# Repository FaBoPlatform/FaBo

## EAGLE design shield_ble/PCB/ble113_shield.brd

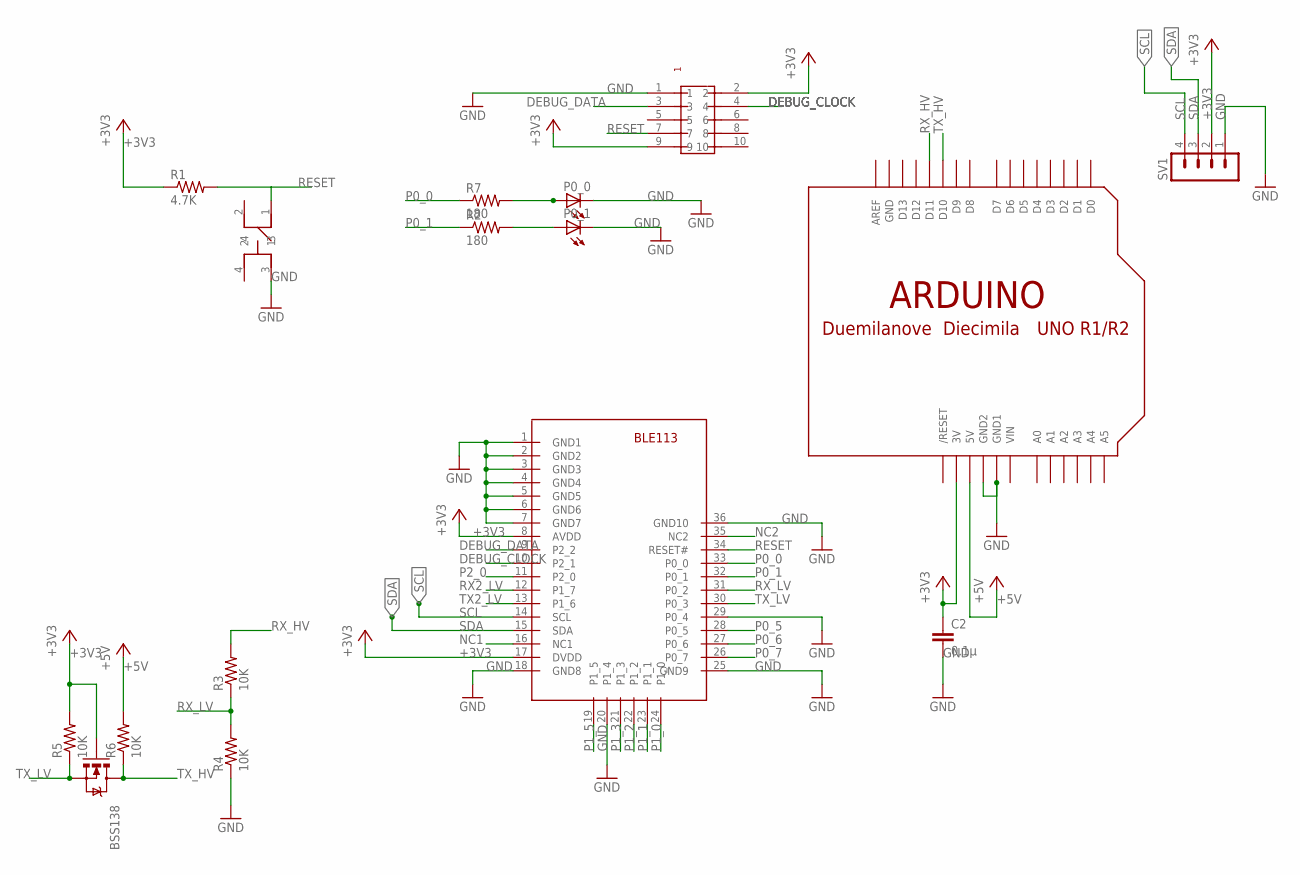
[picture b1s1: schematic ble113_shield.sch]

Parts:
BSS138: MOSFET-NCHANNELSMD; SOT23-3
C2: 0.1μ; 0603-CAP
P0_0, P0_1: LED_ESML0603; LED_SML0603
R1: 4.7K; 0603-RES
R2, R7: 180; 0603-RES
R3, R4, R5, R6: 10K; 0603-RES
SV1: MA04-1
U$1: PIN-HEADER-SMT(1.27MM)2X5
U$4: SWITCH-LS6J2M-T; SWICTH-LS6J2M-T
U$6: BLUEGIGA-BLE113
U$7: ARDUINOUNO; ARDUINO

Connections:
+3V3: BSS138.1 (G), C2.1, R1.1, R5.2, SV1.2, U$1.2, U$1.9, U$6.8 (AVDD), U$6.17 (DVDD), U$7.3V
+5V: R6.2, U$7.5V
DEBUG_CLOCK: U$1.4, U$6.10 (P2_1)
DEBUG_DATA: U$1.3, U$6.9 (P2_2)
GND: C2.2, P0_0.C, P0_1.C, R4.1, SV1.1, U$1.1, U$4.3, U$6.1 (GND1), U$6.2 (GND2), U$6.3 (GND3), U$6.4 (GND4), U$6.5 (GND5), U$6.6 (GND6), U$6.7 (GND7), U$6.18 (GND8), U$6.20 (P1_4), U$6.25 (GND9), U$6.29 (P0_4), U$6.36 (GND10), U$7.GND, U$7.GND1, U$7.GND2
unnamed: P0_0.A, R7.2
unnamed: P0_1.A, R2.2
NC1: U$6.16 (NC1)
NC2: U$6.35 (NC2)
P0_0: R7.1, U$6.33 (P0_0)
P0_1: R2.1, U$6.32 (P0_1)
P0_5: U$6.28 (P0_5)
P0_6: U$6.27 (P0_6)
P0_7: U$6.26 (P0_7)
P1_0: U$6.24 (P1_0)
P1_1: U$6.23 (P1_1)
P1_2: U$6.22 (P1_2)
P1_3: U$6.21 (P1_3)
P1_5: U$6.19 (P1_5)
P2_0: U$6.11 (P2_0)
RESET: R1.2, U$1.7, U$4.1, U$6.34 (RESET#)
RX2_LV: U$6.12 (P1_7)
RX_HV: R3.2, U$7.D11
RX_LV: R3.1, R4.2, U$6.31 (P0_2)
SCL: SV1.4, U$6.14 (SCL)
SDA: SV1.3, U$6.15 (SDA)
TX2_LV: U$6.13 (P1_6)
TX_HV: BSS138.3 (D), R6.1, U$7.D10
TX_LV: BSS138.2 (S), R5.1, U$6.30 (P0_3)
VIN: U$7.VIN

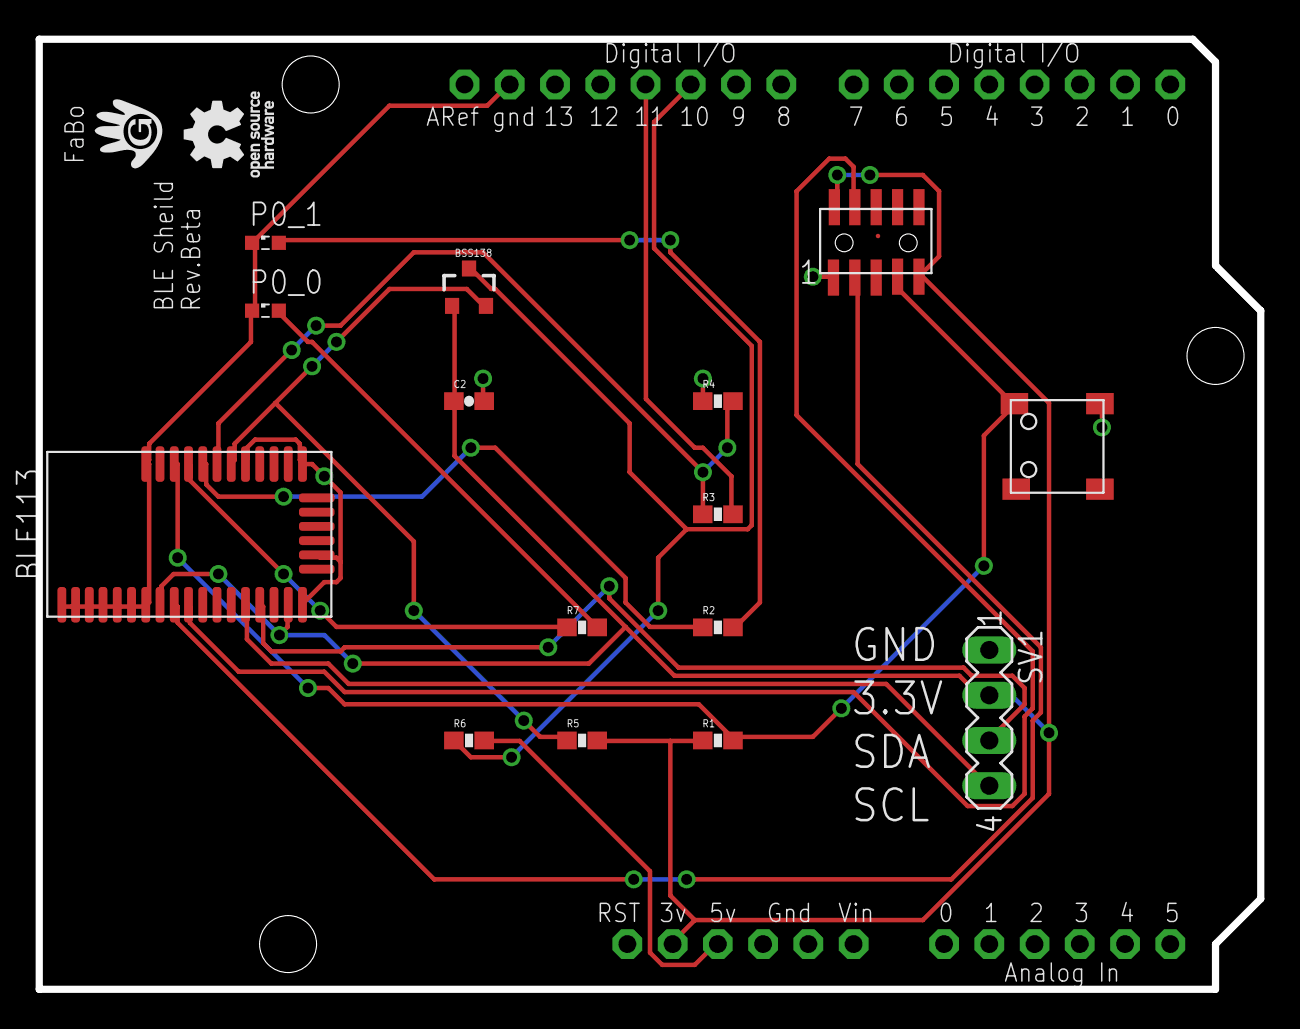
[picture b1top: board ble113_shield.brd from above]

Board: 2 copper layers, 68.6 x 53.3 mm, 18 parts (0 on the bottom side), 16 nets.

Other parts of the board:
U$2: LOGO_FABO_M
U$3: LOGO_OSHW_T_M

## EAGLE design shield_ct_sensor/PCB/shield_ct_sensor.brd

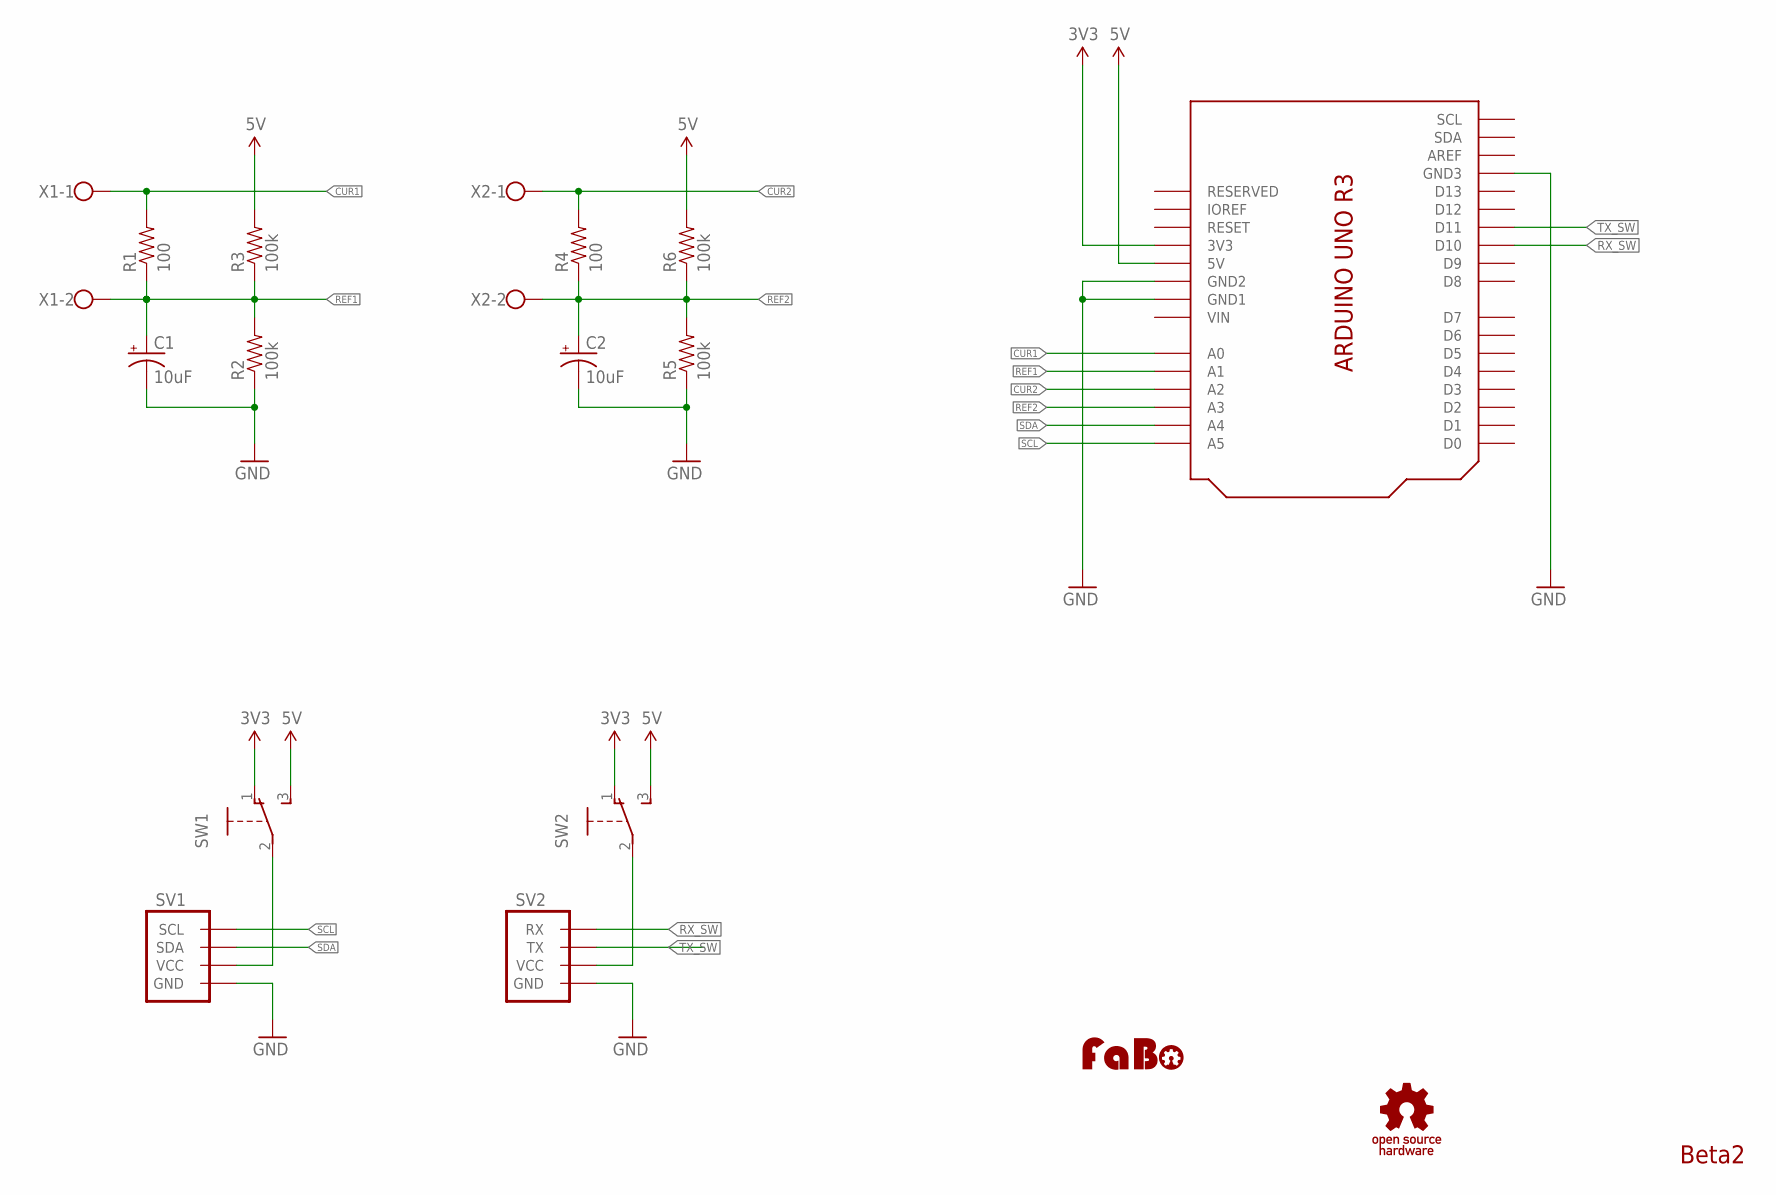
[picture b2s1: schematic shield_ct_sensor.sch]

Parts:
C1, C2: 10uF; CAP-POL-AXL-5MM
R1, R4: 100; RES-AXL-REGULAR
R2, R3, R5, R6: 100k; RES-AXL-REGULAR
SV1: BRICK_I2C_CONNECTOR
SV2: BRICK_SERIAL_CONNECTOR
SW1, SW2: SWITCH-SLIDE-EG1218; EG1218
U1: ARDUINO_UNO_R3_SHIELD; ARDUINO_UNO_R3
U$2: LOGO_FABO-M; LOGO_FABO_M
U$3: LOGO_OSHW_T-M; LOGO_OSHW_T_M
X1, X2: W237-102

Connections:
3V3: SW1.1, SW2.1, U1.3V3
5V: R3.P$2 (2), R6.P$2 (2), SW1.3, SW2.3, U1.5V
CUR1: R1.P$2 (2), U1.A0, X1.1
CUR2: R4.P$2 (2), U1.A2, X2.1
GND: C1.-, C2.-, R2.P$1 (1), R5.P$1 (1), SV1.GND, SV2.GND, U1.GND1, U1.GND2, U1.GND3
unnamed: SV2.VCC, SW2.2
unnamed: SV1.VCC, SW1.2
REF1: C1.+, R1.P$1 (1), R2.P$2 (2), R3.P$1 (1), U1.A1, X1.2
REF2: C2.+, R4.P$1 (1), R5.P$2 (2), R6.P$1 (1), U1.A3, X2.2
RX_SW: SV2.RX, U1.D10
SCL: SV1.SCL, U1.A5
SDA: SV1.SDA, U1.A4
TX_SW: SV2.TX, U1.D11
VIN: U1.VIN

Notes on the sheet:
Beta2

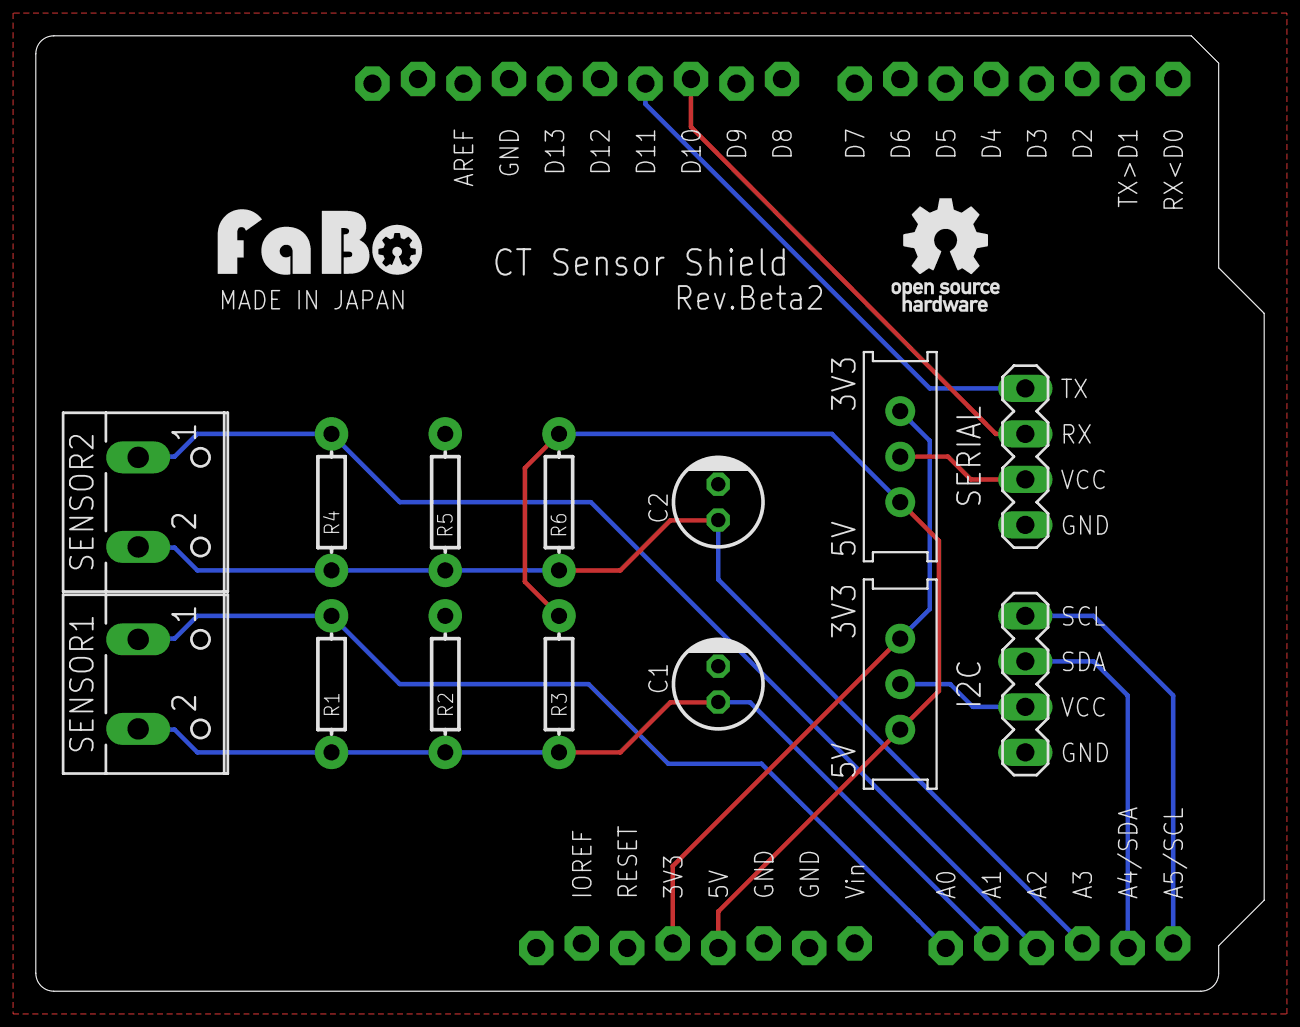
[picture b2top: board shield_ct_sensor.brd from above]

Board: 2 copper layers, 68.6 x 53.3 mm, 17 parts (0 on the bottom side), 13 nets.

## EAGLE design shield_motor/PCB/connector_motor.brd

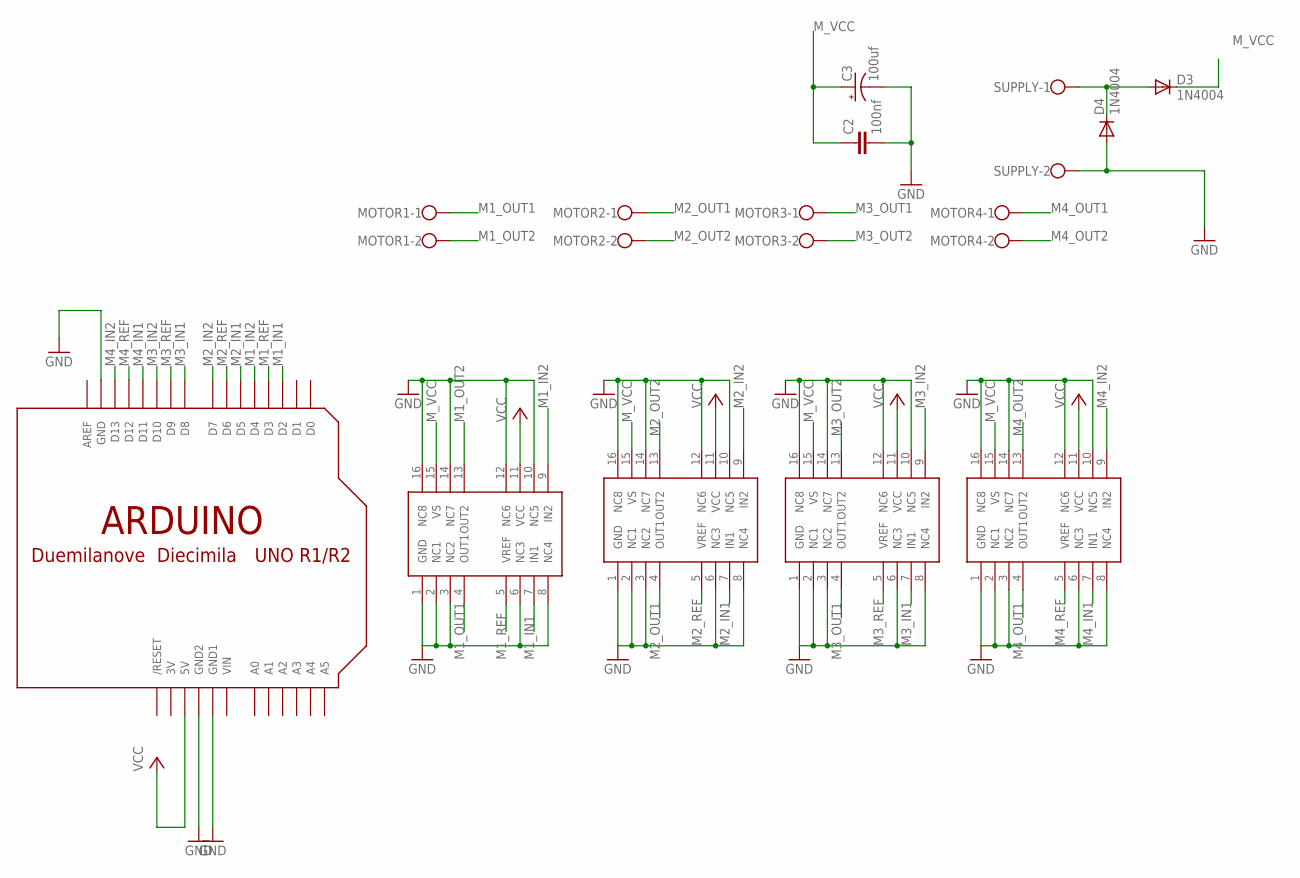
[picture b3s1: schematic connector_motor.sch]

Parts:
C2: 100nf; C0603
C3: 100uf; 153CLV-0405
D3, D4: 1N4004; DO41-10
MOTOR1, MOTOR2, MOTOR3, MOTOR4: W237-102
SUPPLY: W237-102
U$1: ARDUINO-NOHOLE
U$2, U$3, U$4, U$5: MOTOR-DRIVER-TA7281FG; MOTOR-DRIVER-TA7291FG

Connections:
3V: U$1.3V
GND: C2.2, C3.-, D4.A, SUPPLY.2, U$1.GND, U$1.GND1, U$1.GND2, U$2.1 (GND), U$2.2 (NC1), U$2.3 (NC2), U$2.6 (NC3), U$2.8 (NC4), U$2.10 (NC5), U$2.12 (NC6), U$2.14 (NC7), U$2.16 (NC8), U$3.1 (GND), U$3.2 (NC1), U$3.3 (NC2), U$3.6 (NC3), U$3.8 (NC4), U$3.10 (NC5), U$3.12 (NC6), U$3.14 (NC7), U$3.16 (NC8), U$4.1 (GND), U$4.2 (NC1), U$4.3 (NC2), U$4.6 (NC3), U$4.8 (NC4), U$4.10 (NC5), U$4.12 (NC6), U$4.14 (NC7), U$4.16 (NC8), U$5.1 (GND), U$5.2 (NC1), U$5.3 (NC2), U$5.6 (NC3), U$5.8 (NC4), U$5.10 (NC5), U$5.12 (NC6), U$5.14 (NC7), U$5.16 (NC8)
M1_IN1: U$1.D2, U$3.7 (IN1)
M1_IN2: U$1.D4, U$3.9 (IN2)
M1_OUT1: MOTOR1.1, U$3.4 (OUT1)
M1_OUT2: MOTOR1.2, U$3.13 (OUT2)
M1_REF: U$1.D3, U$3.5 (VREF)
M2_IN1: U$1.D5, U$4.7 (IN1)
M2_IN2: U$1.D7, U$4.9 (IN2)
M2_OUT1: MOTOR2.1, U$4.4 (OUT1)
M2_OUT2: MOTOR2.2, U$4.13 (OUT2)
M2_REF: U$1.D6, U$4.5 (VREF)
M3_IN1: U$1.D8, U$2.7 (IN1)
M3_IN2: U$1.D10, U$2.9 (IN2)
M3_OUT1: MOTOR3.1, U$2.4 (OUT1)
M3_OUT2: MOTOR3.2, U$2.13 (OUT2)
M3_REF: U$1.D9, U$2.5 (VREF)
M4_IN1: U$1.D11, U$5.7 (IN1)
M4_IN2: U$1.D13, U$5.9 (IN2)
M4_OUT1: MOTOR4.1, U$5.4 (OUT1)
M4_OUT2: MOTOR4.2, U$5.13 (OUT2)
M4_REF: U$1.D12, U$5.5 (VREF)
M_VCC: C2.1, C3.+, D3.C, U$2.15 (VS), U$3.15 (VS), U$4.15 (VS), U$5.15 (VS)
unnamed: D3.A, D4.C, SUPPLY.1
VCC: U$1.5V, U$2.11 (VCC), U$3.11 (VCC), U$4.11 (VCC), U$5.11 (VCC)
VIN: U$1.VIN

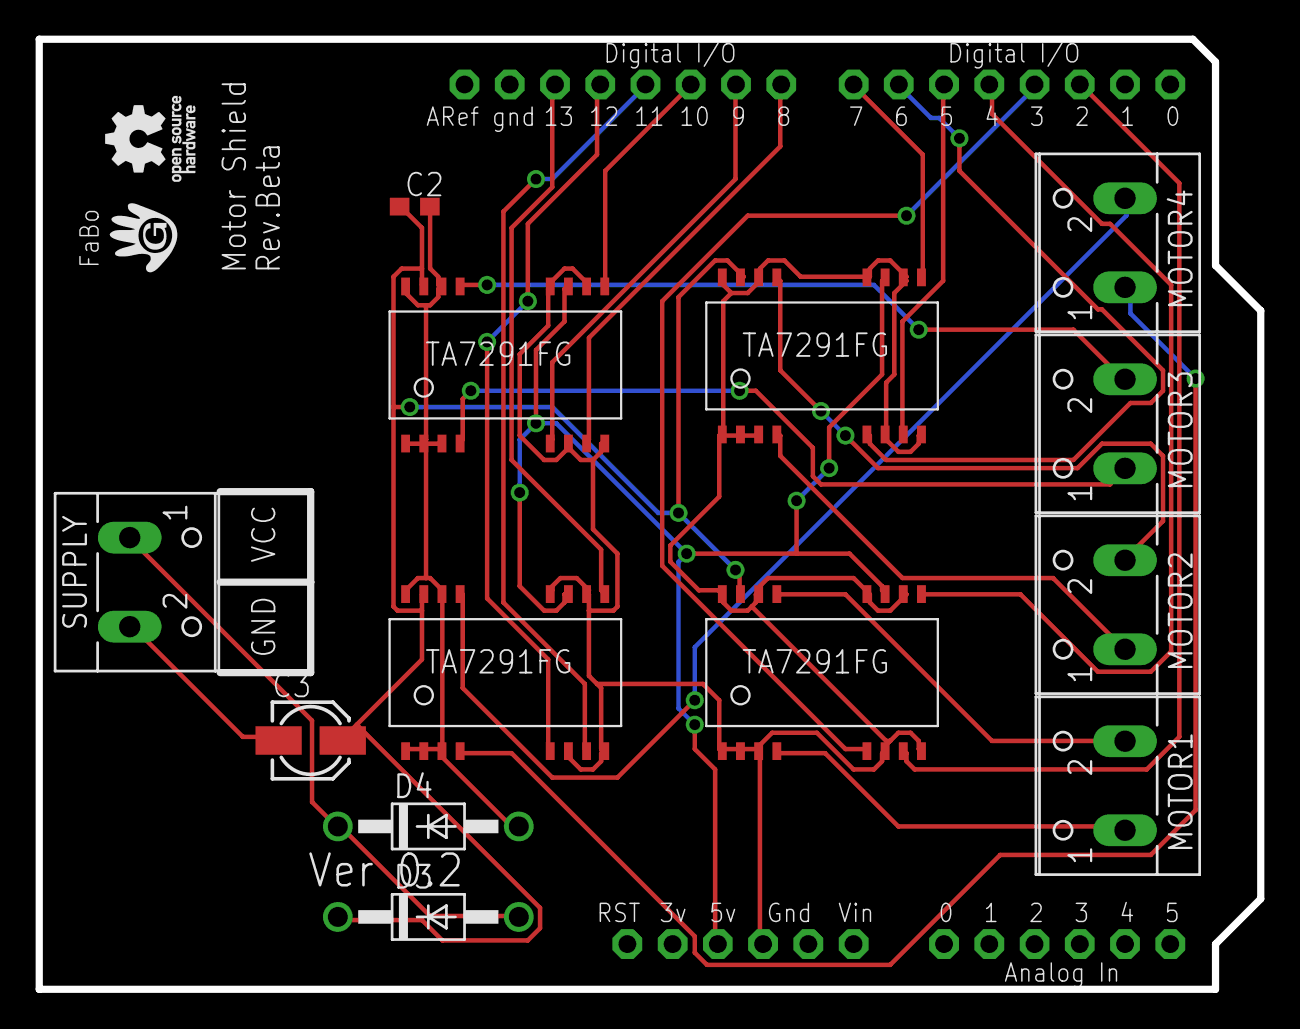
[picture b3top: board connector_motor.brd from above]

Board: 2 copper layers, 68.6 x 53.3 mm, 16 parts (0 on the bottom side), 24 nets.

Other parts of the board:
U$6: LOGO_OSHW_T_M
U$7: LOGO_FABO_M

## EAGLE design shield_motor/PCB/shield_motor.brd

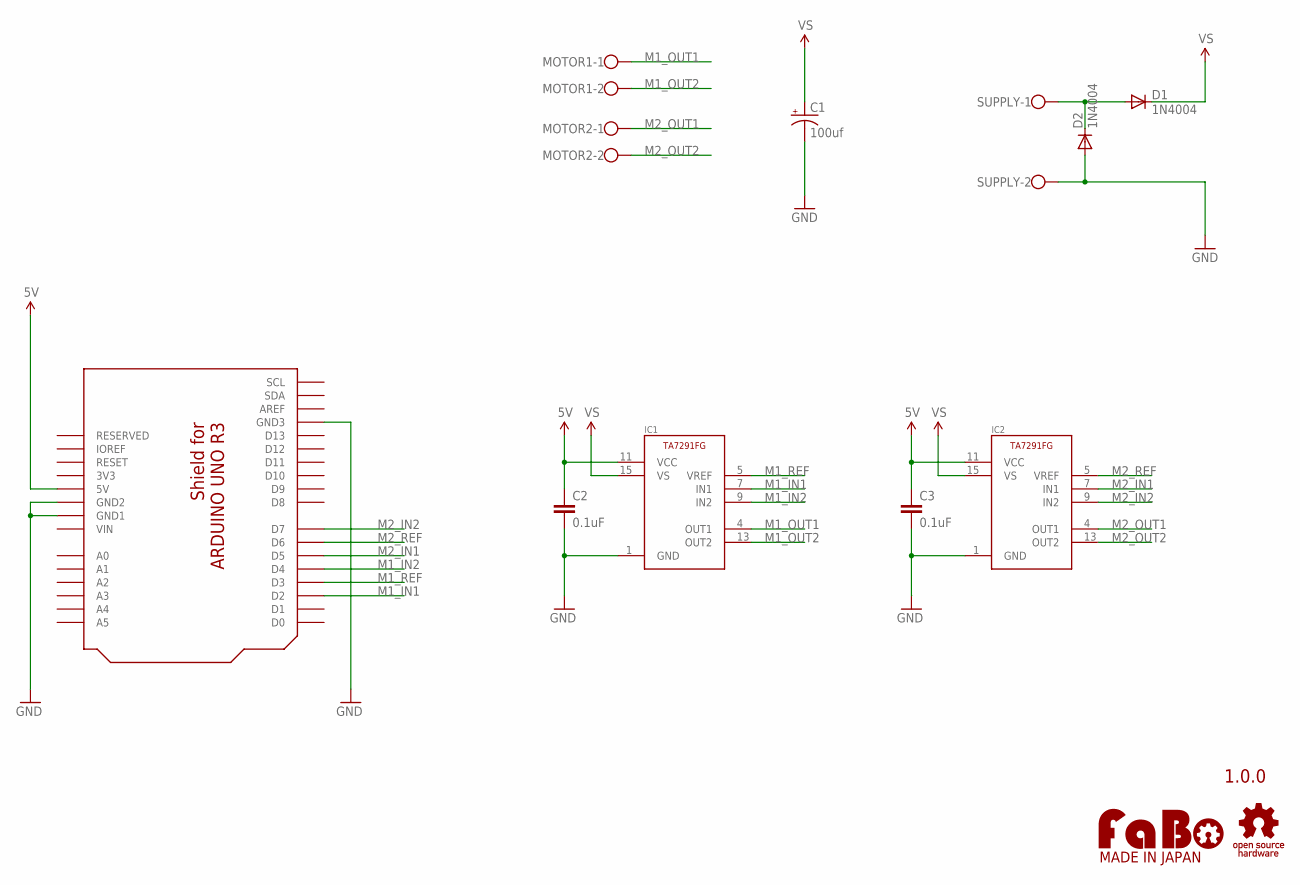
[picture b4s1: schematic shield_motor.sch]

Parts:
C1: 100uf; 153CLV-0405
C2, C3: 0.1uF; EIA0603
D1, D2: 1N4004; DO41-10
IC1, IC2: MOTOR-DRIVER-TA7291FG
MOTOR1, MOTOR2: W237-102
SUPPLY: W237-102
U1: ARDUINO_UNO_R3_SHIELD-NOLABEL; ARDUINO_UNO_R3_NOLABEL
U$6: LOGO_OSHW-T_M; LOGO_OSHW_T_M
U$7: LOGO_FABO-M; LOGO_FABO_M

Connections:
3V3: U1.3V3
5V: C2.1, C3.1, IC1.11 (VCC), IC2.11 (VCC), U1.5V
GND: C1.-, C2.2, C3.2, D2.A, IC1.1 (GND), IC2.1 (GND), SUPPLY.2, U1.GND1, U1.GND2, U1.GND3
M1_IN1: IC1.7 (IN1), U1.D2
M1_IN2: IC1.9 (IN2), U1.D4
M1_OUT1: IC1.4 (OUT1), MOTOR1.1
M1_OUT2: IC1.13 (OUT2), MOTOR1.2
M1_REF: IC1.5 (VREF), U1.D3
M2_IN1: IC2.7 (IN1), U1.D5
M2_IN2: IC2.9 (IN2), U1.D7
M2_OUT1: IC2.4 (OUT1), MOTOR2.1
M2_OUT2: IC2.13 (OUT2), MOTOR2.2
M2_REF: IC2.5 (VREF), U1.D6
unnamed: D1.A, D2.C, SUPPLY.1
VIN: U1.VIN
VS: C1.+, D1.C, IC1.15 (VS), IC2.15 (VS)

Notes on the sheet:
1.0.0

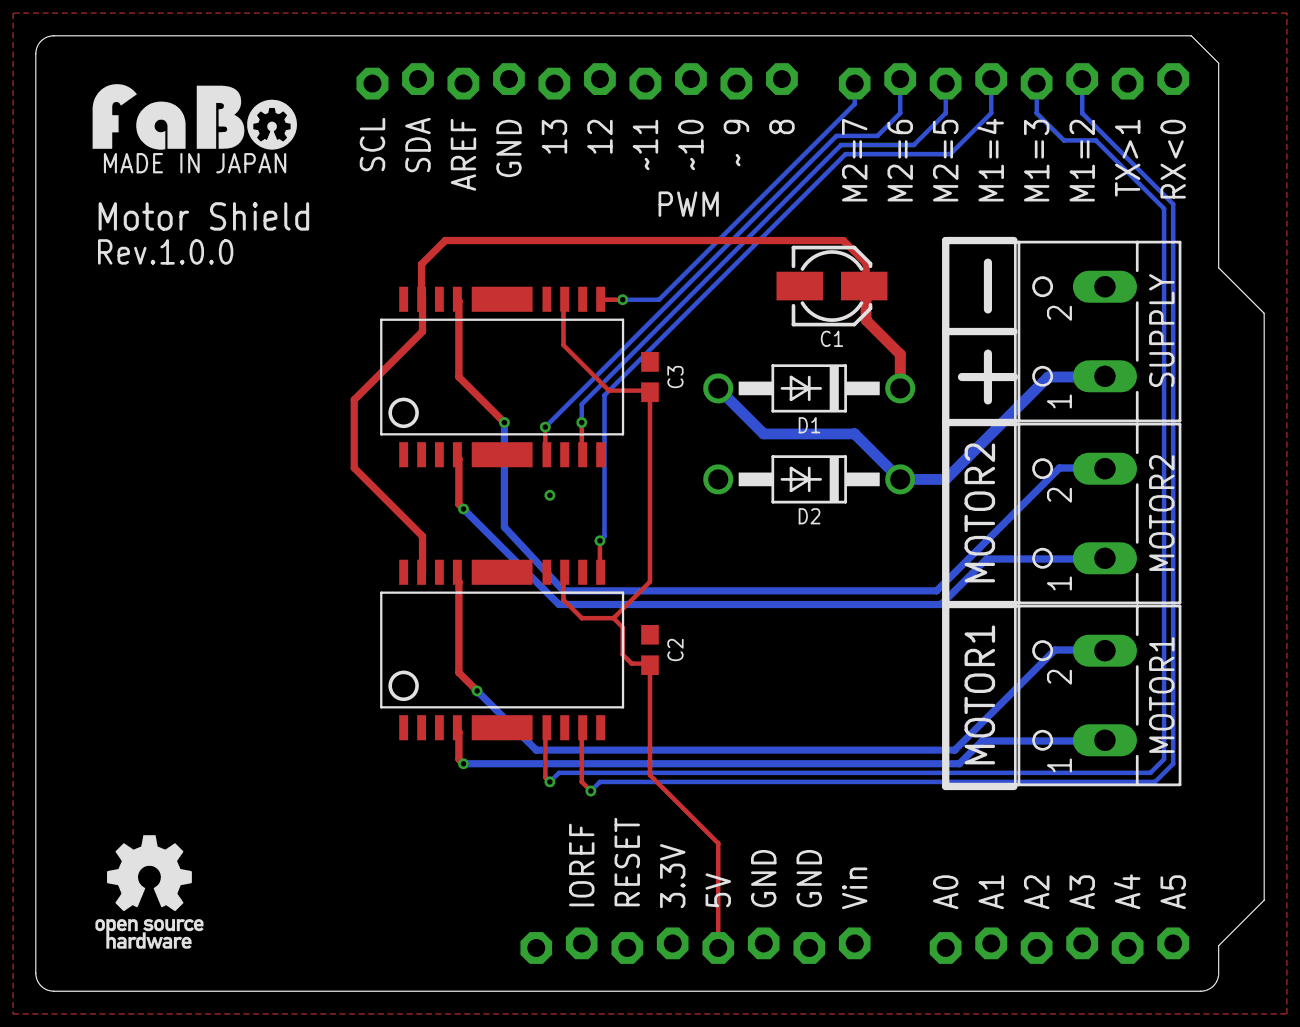
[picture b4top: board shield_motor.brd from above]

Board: 2 copper layers, 68.6 x 53.3 mm, 13 parts (0 on the bottom side), 14 nets.

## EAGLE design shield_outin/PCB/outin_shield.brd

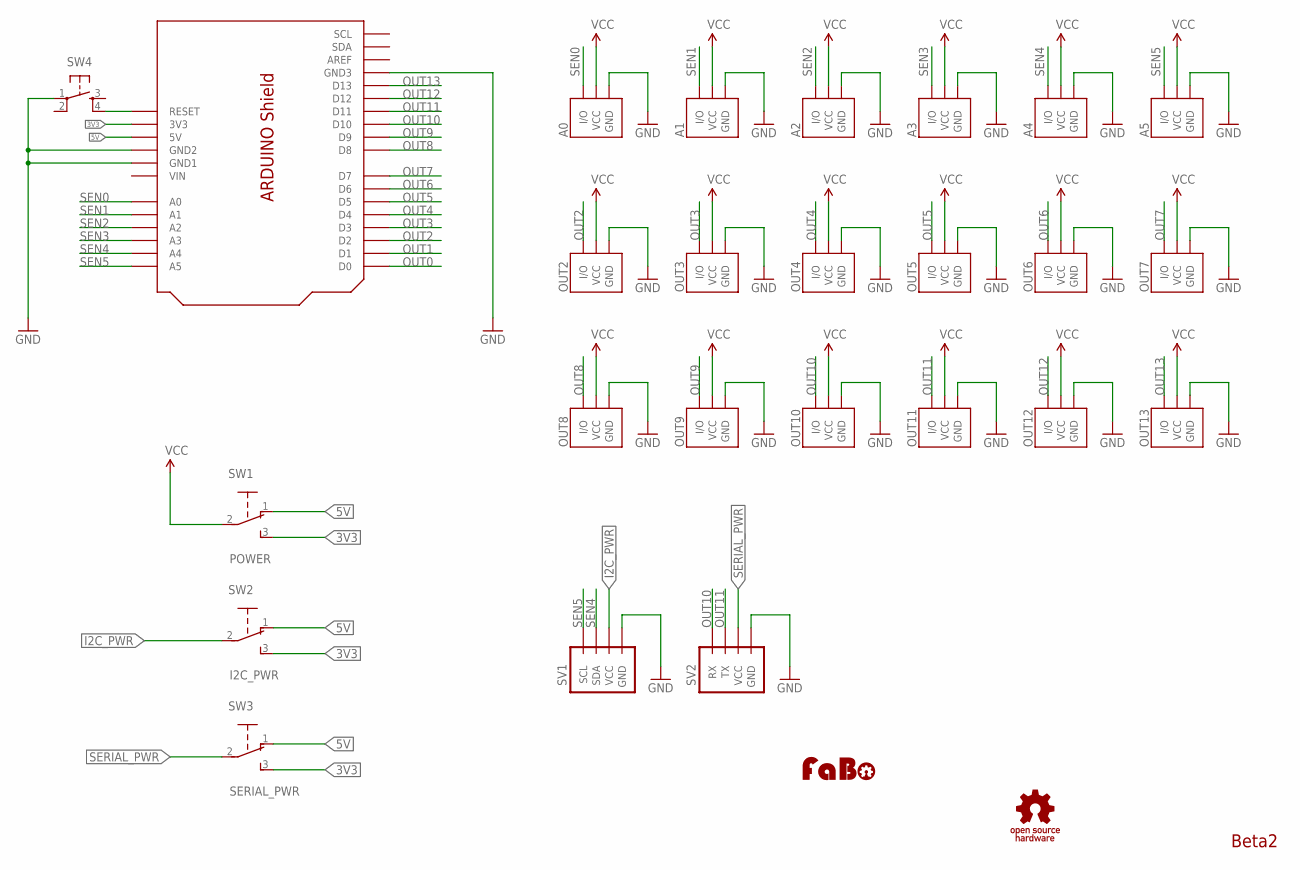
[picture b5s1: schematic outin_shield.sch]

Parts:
A0, A1, A2, A3, A4, A5: IO_PIN-3PIN; 1X3-SNEAKY
OUT2, OUT3, OUT4, OUT5, OUT6, OUT7, OUT8, OUT9, OUT10, OUT11, OUT12, OUT13: IO_PIN-3PIN; 1X3-SNEAKY
SV1: BRICK_I2C_CONNECTOR
SV2: BRICK_SERIAL_CONNECTOR
SW1: POWER; EG1218
SW2: I2C_PWR; EG1218
SW3: SERIAL_PWR; EG1218
SW4: SWITCH-TACT-6MM; DTS_6_V
U1: OUTIN_SHIELD; ARDUINO_UNO_R3_OUTIN
U$4: LOGO_OSHW_T-M; LOGO_OSHW_T_M
U$5: LOGO_FABO-M; LOGO_FABO_M

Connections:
3V3: SW1.3, SW2.3, SW3.3, U1.3V3
5V: SW1.1, SW2.1, SW3.1, U1.5V
GND: A0.1 (GND), A1.1 (GND), A2.1 (GND), A3.1 (GND), A4.1 (GND), A5.1 (GND), OUT2.1 (GND), OUT3.1 (GND), OUT4.1 (GND), OUT5.1 (GND), OUT6.1 (GND), OUT7.1 (GND), OUT8.1 (GND), OUT9.1 (GND), OUT10.1 (GND), OUT11.1 (GND), OUT12.1 (GND), OUT13.1 (GND), SV1.GND, SV2.GND, SW4.1, U1.GND1, U1.GND2, U1.GND3
I2C_PWR: SV1.VCC, SW2.2
OUT0: U1.D0
OUT1: U1.D1
OUT2: OUT2.3 (I/O), U1.D2
OUT3: OUT3.3 (I/O), U1.D3
OUT4: OUT4.3 (I/O), U1.D4
OUT5: OUT5.3 (I/O), U1.D5
OUT6: OUT6.3 (I/O), U1.D6
OUT7: OUT7.3 (I/O), U1.D7
OUT8: OUT8.3 (I/O), U1.D8
OUT9: OUT9.3 (I/O), U1.D9
OUT10: OUT10.3 (I/O), SV2.RX, U1.D10
OUT11: OUT11.3 (I/O), SV2.TX, U1.D11
OUT12: OUT12.3 (I/O), U1.D12
OUT13: OUT13.3 (I/O), U1.D13
RESET: SW4.4, U1.RESET
SEN0: A0.3 (I/O), U1.A0
SEN1: A1.3 (I/O), U1.A1
SEN2: A2.3 (I/O), U1.A2
SEN3: A3.3 (I/O), U1.A3
SEN4: A4.3 (I/O), SV1.SDA, U1.A4
SEN5: A5.3 (I/O), SV1.SCL, U1.A5
SERIAL_PWR: SV2.VCC, SW3.2
VCC: A0.2 (VCC), A1.2 (VCC), A2.2 (VCC), A3.2 (VCC), A4.2 (VCC), A5.2 (VCC), OUT2.2 (VCC), OUT3.2 (VCC), OUT4.2 (VCC), OUT5.2 (VCC), OUT6.2 (VCC), OUT7.2 (VCC), OUT8.2 (VCC), OUT9.2 (VCC), OUT10.2 (VCC), OUT11.2 (VCC), OUT12.2 (VCC), OUT13.2 (VCC), SW1.2
VIN: U1.VIN

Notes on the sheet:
Beta2

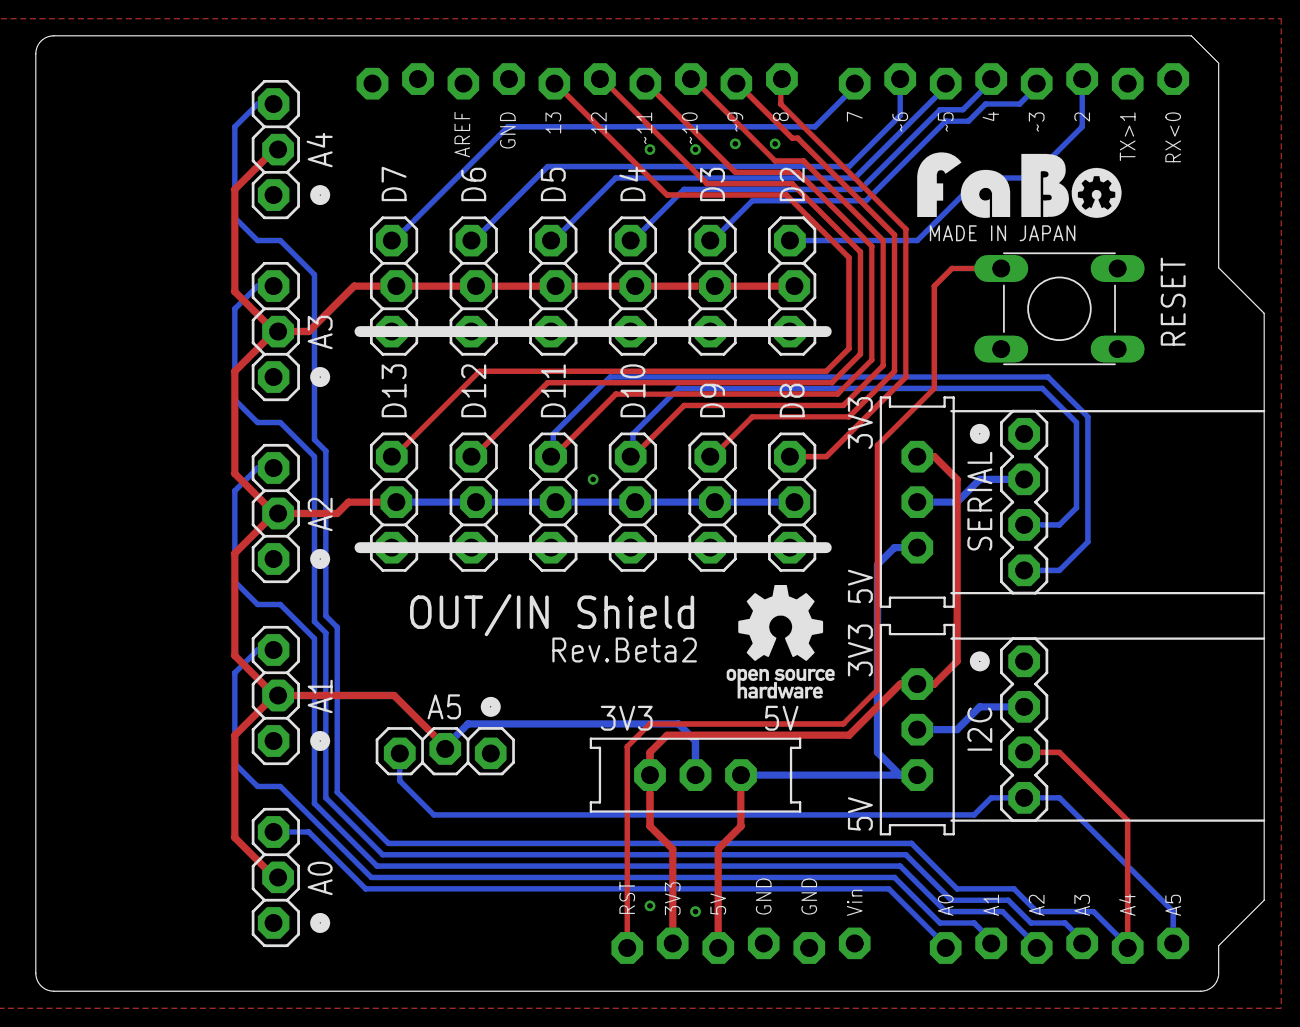
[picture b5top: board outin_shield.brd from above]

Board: 2 copper layers, 68.6 x 53.3 mm, 27 parts (0 on the bottom side), 25 nets.

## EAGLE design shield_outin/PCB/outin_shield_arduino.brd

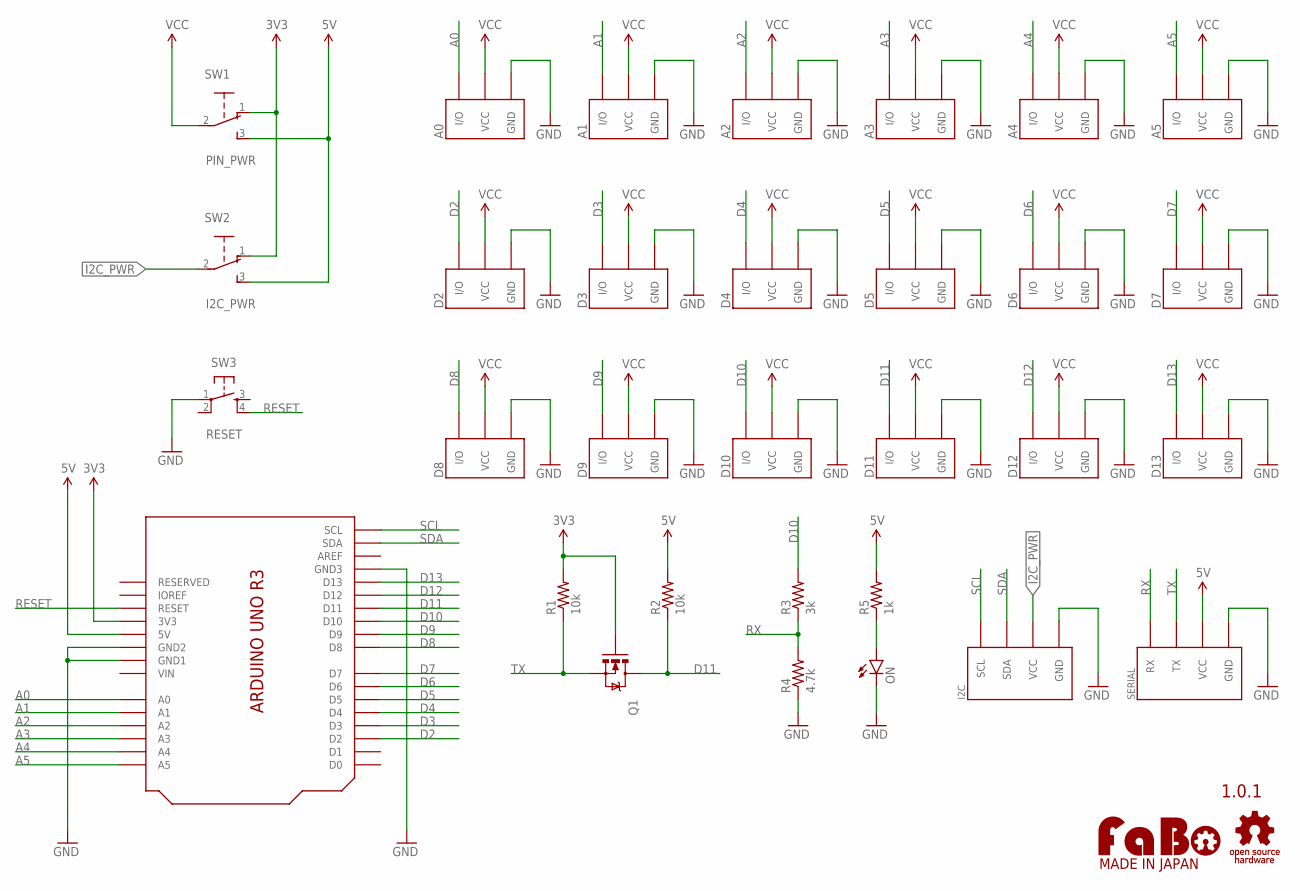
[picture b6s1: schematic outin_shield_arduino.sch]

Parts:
A0, A1, A2, A3, A4, A5: FABO_BRICK_3PIN-CONNECTOR; FABO_BRICK_3PIN_CONNECTOR
D2, D3, D4, D5, D6, D7, D8, D9, D10, D11, D12, D13: FABO_BRICK_3PIN-HEADER; FABO_BRICK_3PIN_HEADER
I2C: FABO_BRICK_I2C-CONNECTOR; FABO_BRICK_I2C_CONNECTOR
ON: LED-EIA0603; EIA0603-LED
Q1: MOSFET-N-BSS138; SOT23-3
R1, R2: 10k; EIA0603
R3: 3k; EIA0603
R4: 4.7k; EIA0603
R5: 1k; EIA0603
SERIAL: FABO_BRICK_SERIAL-CONNECTOR; FABO_BRICK_SERIAL_CONNECTOR
SW1: PIN_PWR; EG1218
SW2: I2C_PWR; EG1218
SW3: RESET; DTS_6_V
U1: ARDUINO_UNO_R3_SHIELD-NOLABEL; ARDUINO_UNO_R3_NOLABEL
U$21: LOGO_FABO-M; LOGO_FABO_M
U$22: LOGO_OSHW-T_M_BOTTOM; LOGO_OSHW_T_M_BOTTOM

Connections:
3V3: Q1.1 (G), R1.2, SW1.1, SW2.1, U1.3V3
5V: R2.2, R5.2, SERIAL.VCC, SW1.3, SW2.3, U1.5V
A0: A0.IN/OUT (I/O), U1.A0
A1: A1.IN/OUT (I/O), U1.A1
A2: A2.IN/OUT (I/O), U1.A2
A3: A3.IN/OUT (I/O), U1.A3
A4: A4.IN/OUT (I/O), U1.A4
A5: A5.IN/OUT (I/O), U1.A5
D2: D2.I/O, U1.D2
D3: D3.I/O, U1.D3
D4: D4.I/O, U1.D4
D5: D5.I/O, U1.D5
D6: D6.I/O, U1.D6
D7: D7.I/O, U1.D7
D8: D8.I/O, U1.D8
D9: D9.I/O, U1.D9
D10: D10.I/O, R3.2, U1.D10
D11: D11.I/O, Q1.3 (D), R2.1, U1.D11
D12: D12.I/O, U1.D12
D13: D13.I/O, U1.D13
GND: A0.GND, A1.GND, A2.GND, A3.GND, A4.GND, A5.GND, D2.GND, D3.GND, D4.GND, D5.GND, D6.GND, D7.GND, D8.GND, D9.GND, D10.GND, D11.GND, D12.GND, D13.GND, I2C.GND, ON.C, R4.1, SERIAL.GND, SW3.1, U1.GND1, U1.GND2, U1.GND3
I2C_PWR: I2C.VCC, SW2.2
LEDANO: ON.A, R5.1
RESET: SW3.4, U1.RESET
RX: R3.1, R4.2, SERIAL.RX
SCL: I2C.SCL, U1.SCL
SDA: I2C.SDA, U1.SDA
TX: Q1.2 (S), R1.1, SERIAL.TX
VCC: A0.VCC, A1.VCC, A2.VCC, A3.VCC, A4.VCC, A5.VCC, D2.VCC, D3.VCC, D4.VCC, D5.VCC, D6.VCC, D7.VCC, D8.VCC, D9.VCC, D10.VCC, D11.VCC, D12.VCC, D13.VCC, SW1.2
VIN: U1.VIN

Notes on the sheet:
1.0.1

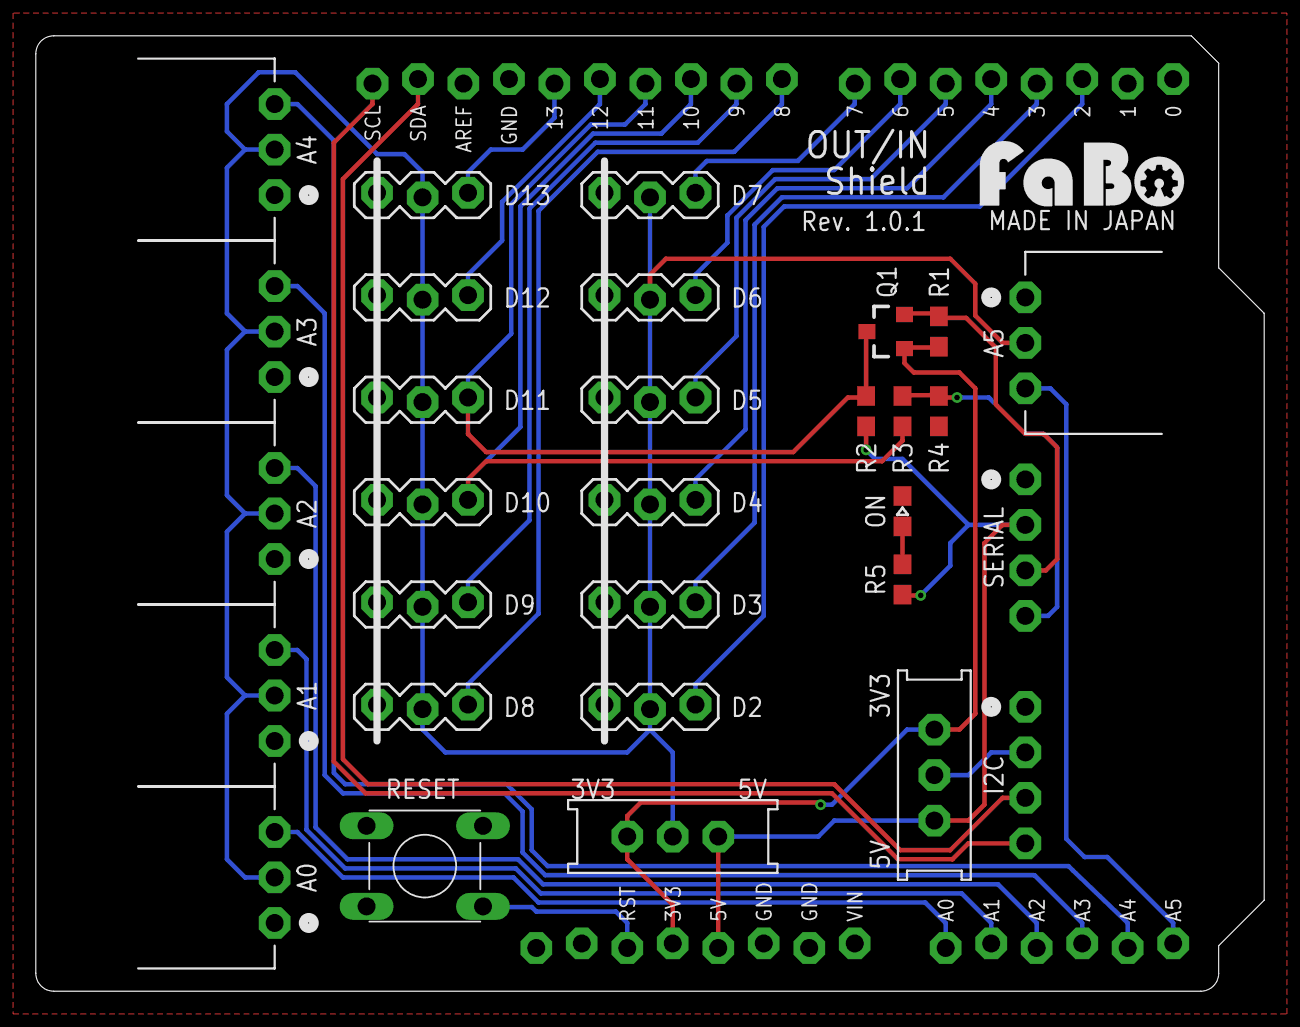
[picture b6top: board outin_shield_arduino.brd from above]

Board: 2 copper layers, 68.6 x 53.3 mm, 33 parts (0 on the bottom side), 29 nets.

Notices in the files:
parts and their libraries:
SparkFun: Licensing: CC v3.0 Share-Alike You are welcome to use this library for commercial purposes.
FaBo-etc: Released under the Creative Commons Attribution-ShareAlike 4.0 License
https://creativecommons.org/licenses/by-sa/4.0
FaBo-etc: Released under the Creative Commons
